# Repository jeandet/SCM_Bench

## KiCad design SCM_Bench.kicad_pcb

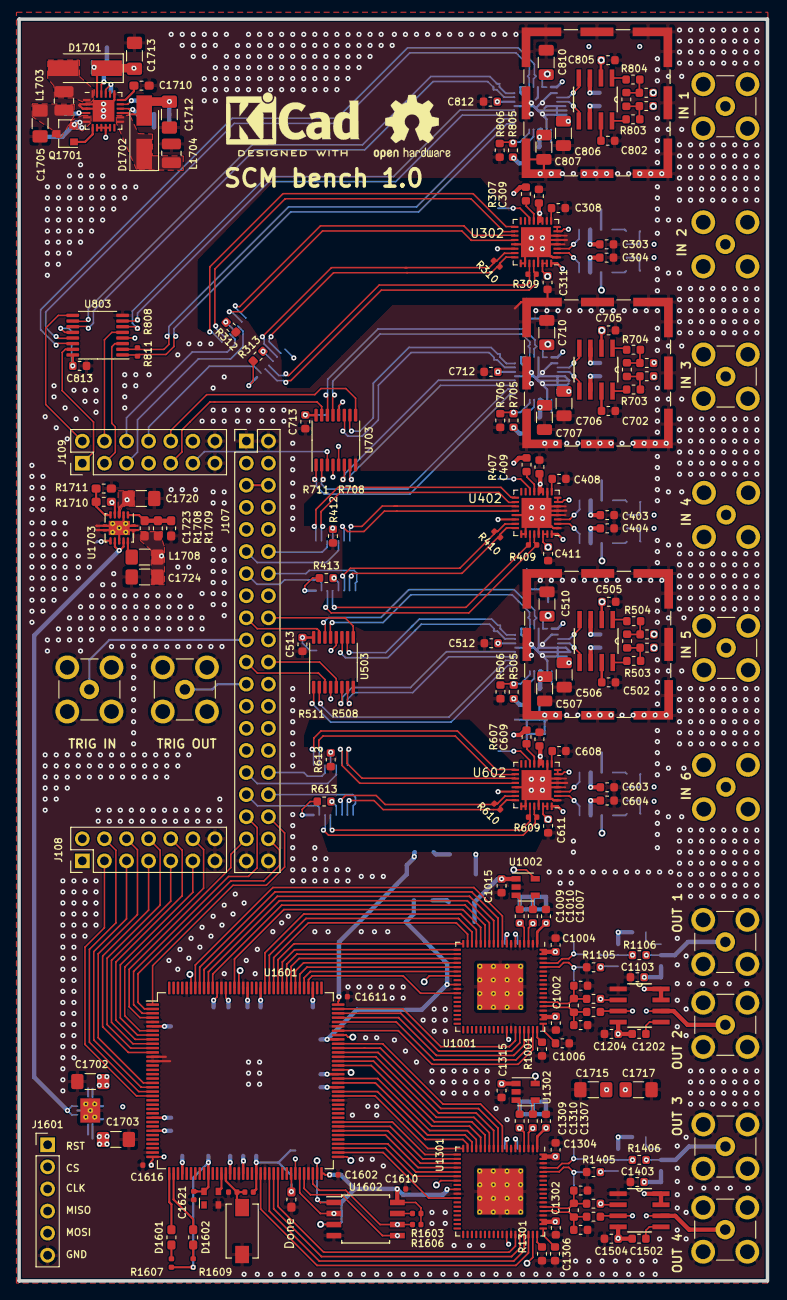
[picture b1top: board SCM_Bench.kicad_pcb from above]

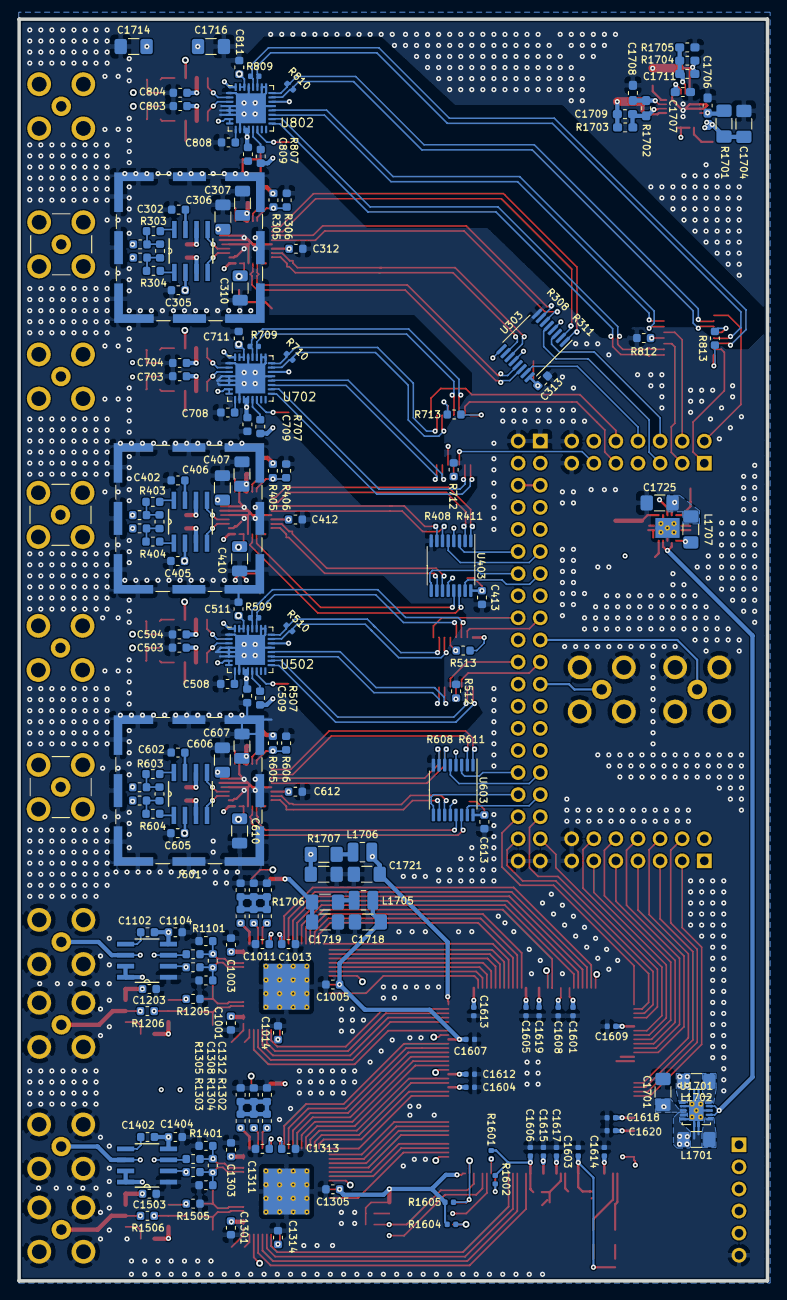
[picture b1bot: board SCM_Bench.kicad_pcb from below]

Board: 4 copper layers, 86.0 x 145.0 mm, 374 parts (186 on the bottom side), 313 nets.

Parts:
C301, C401, C501, C601, C701, C801: 66n; C_0603_1608Metric
C302, C305, C402, C405, C502, C505, C602, C605, C702, C705, C802, C805: 0.01u; C_0603_1608Metric
C303, C304, C308, C309, C311, C312, C313, C403, C404, C408, C409, C411, C412, C413, C503, C504, C508, C509, C511, C512, C513, C603, C604, C608, C609, C611, C612, C613, C703, C704, C708, C709, C711, C712, C713, C803, C804, C808, C809, C811, C812, C813, C1006, C1008, C1009, C1010, C1012, C1101, C1103, C1104, C1201, C1203, C1204, C1306, C1308, C1309, C1310, C1312, C1401, C1403, C1404, C1501, C1503, C1504: 0.1u; C_0603_1608Metric
C306, C307, C310, C406, C407, C410, C506, C507, C510, C606, C607, C610, C706, C707, C710, C806, C807, C810: 10u; C_1206_3216Metric
C1001, C1002, C1003, C1004, C1005, C1007, C1011, C1013, C1014, C1015, C1301, C1302, C1303, C1304, C1305, C1307, C1311, C1313, C1314, C1315: 100n; C_0603_1608Metric
C1102, C1202, C1402, C1502: 7p; C_0603_1608Metric
C1601, C1602, C1603, C1604, C1605, C1606, C1607, C1608, C1609, C1610, C1611, C1612, C1613, C1614, C1615, C1616, C1617, C1618, C1619, C1620, C1621, C1622: 100nF; C_0402_1005Metric
C1701, C1702, C1703, C1720, C1724, C1725: 10uF; C_1206_3216Metric_Pad1.42x1.75mm_HandSolder
C1704, C1705, C1714, C1715, C1716, C1717: 4.7uF; C_1206_3216Metric_Pad1.42x1.75mm_HandSolder
C1706: 100nF; C_0603_1608Metric_Pad1.05x0.95mm_HandSolder
C1707, C1708, C1709, C1710, C1711, C1723: C; C_0603_1608Metric_Pad1.05x0.95mm_HandSolder
C1712, C1713, C1718, C1719, C1721, C1722: 22uF; C_1206_3216Metric_Pad1.42x1.75mm_HandSolder
D1601, D1602: LED; R_0603_1608Metric_Pad1.05x0.95mm_HandSolder
D1701, D1702: D_Schottky; D_SMA_Handsoldering
DONE1601: LED; R_0603_1608Metric_Pad1.05x0.95mm_HandSolder
J101, J102, J103, J104, J105, J106, J110, J111, J901, J902, J903, J904: Conn_Coaxial; SMB_Jack_Vertical
J107: Conn_02x20_Odd_Even; PinHeader_2x20_P2.54mm_Vertical
J108, J109: Conn_02x07_Odd_Even; PinHeader_2x07_P2.54mm_Vertical
J301, J401, J501, J601, J701, J801: RF_Shield_One_Piece; Laird_Technologies_BMI-S-102_16.50x16.50mm
J1601: Conn_01x06; PinHeader_1x06_P2.54mm_Vertical
L1701, L1702, L1707, L1708: 2.2uH; L_1206_3216Metric_Pad1.42x1.75mm_HandSolder
L1703, L1704, L1705, L1706: 4.7uH; L_1008_2520Metric
LOGO101: Logo_Open_Hardware_Small; OSHW-Logo2_9.8x8mm_SilkScreen
LOGO102: Logo_Open_Hardware_Small; KiCad-Logo2_6mm_SilkScreen
Q1701: Q_PMOS_GSD; SOT-23
R301, R302, R303, R304, R401, R402, R403, R404, R501, R502, R503, R504, R601, R602, R603, R604, R701, R702, R703, R704, R801, R802, R803, R804: 1.7k; R_0603_1608Metric
R305, R306, R307, R312, R313, R405, R406, R407, R412, R413, R505, R506, R507, R512, R513, R605, R606, R607, R612, R613, R705, R706, R707, R712, R713, R805, R806, R807, R812, R813, R1001, R1301: 10k; R_0603_1608Metric
R308, R309, R310, R311, R408, R409, R410, R411, R508, R509, R510, R511, R608, R609, R610, R611, R708, R709, R710, R711, R808, R809, R810, R811: 100; R_0402_1005Metric
R1002, R1003, R1302, R1303: 50; R_0603_1608Metric
R1004, R1304: 1K; R_0603_1608Metric
R1005, R1305: 287; R_0603_1608Metric
R1101, R1102, R1201, R1202, R1401, R1402, R1501, R1502: 25; R_0603_1608Metric
R1103, R1104, R1203, R1204, R1403, R1404, R1503, R1504: 225; R_0603_1608Metric
R1105, R1106, R1205, R1206, R1405, R1406, R1505, R1506: 500; R_0603_1608Metric
R1601, R1603, R1604, R1605, R1606: 10k; R_0402_1005Metric
R1602, R1607, R1608, R1609: 2K2; R_0402_1005Metric
R1701: 100; R_1206_3216Metric_Pad1.42x1.75mm_HandSolder
R1702, R1703, R1704, R1705, R1708, R1709, R1710, R1711: R; R_0603_1608Metric_Pad1.05x0.95mm_HandSolder
R1706, R1707: 500m; R_1206_3216Metric_Pad1.42x1.75mm_HandSolder
SW1601: SW_Push; SW_SPST_EVQPE1
U301, U401, U501, U601, U701, U801: LT6600IS8; SOIC127P600X175-8N
U302, U402, U502, U602, U702, U802: LTC2386-18; QFN-32-1EP_5x5mm_P0.5mm_EP3.45x3.45mm
U303, U403, U503, U603, U703, U803: SN65LVDS1050PW; TSSOP-16_4.4x5mm_P0.65mm
U1001, U1301: AD9747BCPZ; LFCSP-72-1EP_10x10mm_P0.5mm_EP5.3x5.3mm_ThermalVias
U1002, U1302: SN65LVDS1DBV; SOT-23-5
U1101, U1201, U1401, U1501: AD8021; SOIC127P600X175-8N
U1601: ICE40HX1K-4K-TQ144; TQFP-144_20x20mm_P0.5mm
U1602: M25PX32-VMW; SOIJ-8_5.3x5.3mm_P1.27mm
U1603: ASDMB-xxxMHz; Oscillator_SMD_Abracon_ASDMB-4Pin_2.5x2.0mm
U1701, U1703: tps6240x; Texas_S-PVSON-N10_ThermalVias
U1702: TPS6513x; HVQFN-24-1EP_4x4mm_P0.5mm_EP2.5x2.5mm

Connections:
/2.5V: C310.1, C311.1, C410.1, C411.1, C510.1, C511.1, C610.1, C611.1, C710.1, C711.1, C810.1, C811.1, C1722.1, R1707.1, U302.30, U302.31, U402.30, U402.31, U502.30, U502.31, U602.30, U602.31, U702.30, U702.31, U802.30, U802.31
/3.3V: C1001.2, C1002.1, C1003.1, C1004.1, C1015.1, C1301.2, C1302.1, C1303.1, C1304.1, C1315.1, C1719.1, R1706.1, U1001.56, U1001.57, U1001.71, U1001.72, U1002.1, U1301.56, U1301.57, U1301.71, U1301.72, U1302.1
/5V: C304.2, C307.1, C309.1, C404.2, C407.1, C409.1, C504.2, C507.1, C509.1, C604.2, C607.1, C609.1, C704.2, C707.1, C709.1, C804.2, C807.1, C809.1, C1103.2, C1203.2, C1403.2, C1503.2, C1711.1, C1713.1, C1716.1, C1717.1, D1701.1, R1704.1, U301.3, U302.11, U302.12, U401.3, U402.11, U402.12, U501.3, U502.11, U502.12, U601.3, U602.11, U602.12, U701.3, U702.11, U702.12, U801.3, U802.11, U802.12, U1101.7, U1101.8, U1201.7, U1201.8, U1401.7, U1401.8, U1501.7, U1501.8, U1702.23
/#1.8V: C1007.1, C1011.1, C1013.1, C1014.1, C1307.1, C1311.1, C1313.1, C1314.1, C1725.1, L1707.2, R1004.2, R1304.2, R1710.1, U1001.1, U1001.6, U1001.8, U1001.47, U1301.1, U1301.6, U1301.8, U1301.47, U1703.4
/#2.5V: C312.1, C313.2, C412.1, C413.2, C512.1, C513.2, C612.1, C613.2, C712.1, C713.2, C812.1, C813.2, C1611.1, C1721.1, C1723.1, C1724.1, L1706.1, L1708.2, R305.2, R307.1, R313.1, R405.2, R407.1, R413.1, R505.2, R507.1, R513.1, R605.2, R607.1, R613.1, R705.2, R707.1, R713.1, R805.2, R807.1, R813.1, R1708.1, U302.22, U303.16, U402.22, U403.16, U502.22, U503.16, U602.22, U603.16, U702.22, U703.16, U802.22, U803.16, U1601.108
/-5V: C303.2, C403.2, C503.2, C603.2, C703.2, C803.2, C1102.1, C1104.1, C1202.1, C1204.1, C1402.1, C1404.1, C1502.1, C1504.1, C1709.2, C1712.1, C1714.1, C1715.1, D1702.2, R1703.2, U301.6, U401.6, U501.6, U601.6, U701.6, U801.6, U1101.4, U1201.4, U1401.4, U1501.4, U1702.15
/ADC1_CLK: J109.2, U803.9
/ADC1_CNV: J109.1, U803.15
/ADC1_DA: J109.3, U803.3
/ADC1_DCO: J109.4, U803.5
/ADC2_CLK: J109.7, U303.9
/ADC2_CNV: J109.8, U303.15
/ADC2_DA: J109.6, U303.3
/ADC2_DCO: J109.5, U303.5
/ADC3_CLK: J109.10, U703.9
/ADC3_CNV: J109.9, U703.15
/ADC3_DA: J109.11, U703.3
/ADC3_DCO: J109.12, U703.5
/ADC4_CLK: J107.14, U403.9
/ADC4_CNV: J107.13, U403.15
/ADC4_DA: J107.12, U403.3
/ADC4_DCO: J107.11, U403.5
/ADC5_CLK: J107.18, U503.9
/ADC5_CNV: J107.17, U503.15
/ADC5_DA: J107.21, U503.3
/ADC5_DCO: J107.22, U503.5
/ADC6_CLK: J107.34, U603.9
/ADC6_CNV: J107.33, U603.15
/ADC6_DA: J107.32, U603.3
/ADC6_DCO: J107.31, U603.5
/DAC_FPGA_IO0: J107.36, U1601.1
/DAC_FPGA_IO1: J107.38, U1601.2
/DAC_FPGA_IO2: J107.35, U1601.3
/DAC_FPGA_IO3: J107.37, U1601.4
/DAC_FPGA_IO4: J108.12, U1601.7
/DAC_FPGA_IO5: J108.11, U1601.8
/DAC_FPGA_IO6: J108.10, U1601.9
/DAC_FPGA_IO7: J108.9, U1601.10
/DAC_FPGA_IO8: J108.8, U1601.11
/DAC_FPGA_IO9: J108.7, U1601.12
/DAC_FPGA_IO10: J108.6, U1601.19
/DAC_FPGA_IO11: J108.5, U1601.20
/DAC_FPGA_IO12: J108.4, U1601.21
/DAC_FPGA_IO13: J108.3, U1601.22
/FLASH_CLK: J107.28, J1601.3, R1606.2, U1601.70, U1602.6
/FLASH_MISO: J107.29, J1601.4, U1601.67, U1602.2
/FLASH_MOSI: J107.30, J1601.5, U1601.68, U1602.5
/FLASH_SS: J107.27, J1601.2, R1605.2, U1601.71, U1602.1
/FLASH_~CRESET: J107.26, J1601.1, R1601.2, U1601.66
/IOB_11: J107.23, J111.1
/IOB_15: J107.19, J110.1
/Sheet5F3E1819/CH1_IN+: J101.1, R801.2
/Sheet5F3E1819/CH1_IN-: J101.2, R802.2
/Sheet5F3E1819/CH2_IN+: J102.1, R301.2
/Sheet5F3E1819/CH2_IN-: J102.2, R302.2
/Sheet5F3E1819/CH3_IN+: J103.1, R701.2
/Sheet5F3E1819/CH3_IN-: J103.2, R702.2
/Sheet5F3E1819/CH4_IN+: J104.1, R401.2
/Sheet5F3E1819/CH4_IN-: J104.2, R402.2
/Sheet5F3E1819/CH5_IN+: J105.1, R501.2
/Sheet5F3E1819/CH5_IN-: J105.2, R502.2
/Sheet5F3E1819/CH6_IN+: J106.1, R601.2
/Sheet5F3E1819/CH6_IN-: J106.2, R602.2
/Sheet5F3E1819/Sheet5F3E1AE4/ADC1_OUT_IN+: U301.4, U302.2
/Sheet5F3E1819/Sheet5F3E1AE4/ADC1_OUT_IN-: U301.5, U302.3
/Sheet5F3E1819/Sheet5F3E1AE4/CLK+: R310.2, U302.24, U303.10
/Sheet5F3E1819/Sheet5F3E1AE4/CLK-: R310.1, U302.23, U303.11
/Sheet5F3E1819/Sheet5F3E1AE4/CNV+: R309.2, U302.28, U303.14
/Sheet5F3E1819/Sheet5F3E1AE4/CNV-: R309.1, U302.27, U303.13
/Sheet5F3E1819/Sheet5F3E1AE4/DA+: R311.2, U302.18, U303.2
/Sheet5F3E1819/Sheet5F3E1AE4/DA-: R311.1, U302.17, U303.1
/Sheet5F3E1819/Sheet5F3E1AE4/DCO+: R308.2, U302.20, U303.6
/Sheet5F3E1819/Sheet5F3E1AE4/DCO-: R308.1, U302.19, U303.7
/Sheet5F3E1819/sheet5F766F53/ADC1_OUT_IN+: U601.4, U602.2
/Sheet5F3E1819/sheet5F766F53/ADC1_OUT_IN-: U601.5, U602.3
/Sheet5F3E1819/sheet5F766F53/CLK+: R610.2, U602.24, U603.10
/Sheet5F3E1819/sheet5F766F53/CLK-: R610.1, U602.23, U603.11
/Sheet5F3E1819/sheet5F766F53/CNV+: R609.2, U602.28, U603.14
/Sheet5F3E1819/sheet5F766F53/CNV-: R609.1, U602.27, U603.13
/Sheet5F3E1819/sheet5F766F53/DA+: R611.2, U602.18, U603.2
/Sheet5F3E1819/sheet5F766F53/DA-: R611.1, U602.17, U603.1
/Sheet5F3E1819/sheet5F766F53/DCO+: R608.2, U602.20, U603.6
/Sheet5F3E1819/sheet5F766F53/DCO-: R608.1, U602.19, U603.7
/Sheet5F3E1819/sheet5F7670FC/ADC1_OUT_IN+: U401.4, U402.2
/Sheet5F3E1819/sheet5F7670FC/ADC1_OUT_IN-: U401.5, U402.3
/Sheet5F3E1819/sheet5F7670FC/CLK+: R410.2, U402.24, U403.10
/Sheet5F3E1819/sheet5F7670FC/CLK-: R410.1, U402.23, U403.11
/Sheet5F3E1819/sheet5F7670FC/CNV+: R409.2, U402.28, U403.14
/Sheet5F3E1819/sheet5F7670FC/CNV-: R409.1, U402.27, U403.13
/Sheet5F3E1819/sheet5F7670FC/DA+: R411.2, U402.18, U403.2
/Sheet5F3E1819/sheet5F7670FC/DA-: R411.1, U402.17, U403.1
/Sheet5F3E1819/sheet5F7670FC/DCO+: R408.2, U402.20, U403.6
/Sheet5F3E1819/sheet5F7670FC/DCO-: R408.1, U402.19, U403.7
/Sheet5F3E1819/sheet5F7672A2/ADC1_OUT_IN+: U801.4, U802.2
/Sheet5F3E1819/sheet5F7672A2/ADC1_OUT_IN-: U801.5, U802.3
/Sheet5F3E1819/sheet5F7672A2/CLK+: R810.2, U802.24, U803.10
/Sheet5F3E1819/sheet5F7672A2/CLK-: R810.1, U802.23, U803.11
/Sheet5F3E1819/sheet5F7672A2/CNV+: R809.2, U802.28, U803.14
/Sheet5F3E1819/sheet5F7672A2/CNV-: R809.1, U802.27, U803.13
/Sheet5F3E1819/sheet5F7672A2/DA+: R811.2, U802.18, U803.2
/Sheet5F3E1819/sheet5F7672A2/DA-: R811.1, U802.17, U803.1
/Sheet5F3E1819/sheet5F7672A2/DCO+: R808.2, U802.20, U803.6
/Sheet5F3E1819/sheet5F7672A2/DCO-: R808.1, U802.19, U803.7
/Sheet5F3E1819/sheet5F76778E/ADC1_OUT_IN+: U701.4, U702.2
/Sheet5F3E1819/sheet5F76778E/ADC1_OUT_IN-: U701.5, U702.3
/Sheet5F3E1819/sheet5F76778E/CLK+: R710.2, U702.24, U703.10
/Sheet5F3E1819/sheet5F76778E/CLK-: R710.1, U702.23, U703.11
/Sheet5F3E1819/sheet5F76778E/CNV+: R709.2, U702.28, U703.14
/Sheet5F3E1819/sheet5F76778E/CNV-: R709.1, U702.27, U703.13
/Sheet5F3E1819/sheet5F76778E/DA+: R711.2, U702.18, U703.2
/Sheet5F3E1819/sheet5F76778E/DA-: R711.1, U702.17, U703.1
/Sheet5F3E1819/sheet5F76778E/DCO+: R708.2, U702.20, U703.6
/Sheet5F3E1819/sheet5F76778E/DCO-: R708.1, U702.19, U703.7
/Sheet5F3E1819/sheet5F767499/ADC1_OUT_IN+: U501.4, U502.2
/Sheet5F3E1819/sheet5F767499/ADC1_OUT_IN-: U501.5, U502.3
/Sheet5F3E1819/sheet5F767499/CLK+: R510.2, U502.24, U503.10
/Sheet5F3E1819/sheet5F767499/CLK-: R510.1, U502.23, U503.11
/Sheet5F3E1819/sheet5F767499/CNV+: R509.2, U502.28, U503.14
/Sheet5F3E1819/sheet5F767499/CNV-: R509.1, U502.27, U503.13
/Sheet5F3E1819/sheet5F767499/DA+: R511.2, U502.18, U503.2
/Sheet5F3E1819/sheet5F767499/DA-: R511.1, U502.17, U503.1
/Sheet5F3E1819/sheet5F767499/DCO+: R508.2, U502.20, U503.6
/Sheet5F3E1819/sheet5F767499/DCO-: R508.1, U502.19, U503.7
/Sheet5F420A25/DAC1_D0: U1001.24, U1601.113
/Sheet5F420A25/DAC1_D1: U1001.23, U1601.114
/Sheet5F420A25/DAC1_D2: U1001.22, U1601.115
/Sheet5F420A25/DAC1_D3: U1001.21, U1601.116
/Sheet5F420A25/DAC1_D4: U1001.20, U1601.117
/Sheet5F420A25/DAC1_D5: U1001.19, U1601.118
/Sheet5F420A25/DAC1_D6: U1001.18, U1601.119
/Sheet5F420A25/DAC1_D7: U1001.17, U1601.120
/Sheet5F420A25/DAC1_D8: U1001.16, U1601.121
/Sheet5F420A25/DAC1_D9: U1001.15, U1601.122
/Sheet5F420A25/DAC1_D10: U1001.14, U1601.129
/Sheet5F420A25/DAC1_D11: U1001.13, U1601.134
/Sheet5F420A25/DAC1_D12: U1001.12, U1601.135
/Sheet5F420A25/DAC1_D13: U1001.11, U1601.136
/Sheet5F420A25/DAC1_D14: U1001.10, U1601.137
/Sheet5F420A25/DAC1_D15: U1001.9, U1601.138
/Sheet5F420A25/DAC2_D0: U1301.24, U1601.75
/Sheet5F420A25/DAC2_D1: U1301.23, U1601.76
/Sheet5F420A25/DAC2_D2: U1301.22, U1601.78
/Sheet5F420A25/DAC2_D3: U1301.21, U1601.79
/Sheet5F420A25/DAC2_D4: U1301.20, U1601.80
/Sheet5F420A25/DAC2_D5: U1301.19, U1601.81
/Sheet5F420A25/DAC2_D6: U1301.18, U1601.87
/Sheet5F420A25/DAC2_D7: U1301.17, U1601.88
/Sheet5F420A25/DAC2_D8: U1301.16, U1601.90
/Sheet5F420A25/DAC2_D9: U1301.15, U1601.91
/Sheet5F420A25/DAC2_D10: U1301.14, U1601.94
/Sheet5F420A25/DAC2_D11: U1301.13, U1601.95
/Sheet5F420A25/DAC2_D12: U1301.12, U1601.96
/Sheet5F420A25/DAC2_D13: U1301.11, U1601.97
/Sheet5F420A25/DAC2_D14: U1301.10, U1601.98
/Sheet5F420A25/DAC2_D15: U1301.9, U1601.99
/Sheet5F420A25/Sheet5F420DB3/CSB: U1001.52, U1601.104
/Sheet5F420A25/Sheet5F420DB3/DAC_CLK_N: C1009.2, U1002.3
/Sheet5F420A25/Sheet5F420DB3/DAC_CLK_P: C1010.2, U1002.4
/Sheet5F420A25/Sheet5F420DB3/OUT1: J902.1, R1106.1, U1101.6
/Sheet5F420A25/Sheet5F420DB3/OUT2: J901.1, R1206.1, U1201.6
/Sheet5F420A25/Sheet5F420DB3/Sheet5F4D5B79/IN+: C1101.2, R1101.2, R1103.2, U1001.69
/Sheet5F420A25/Sheet5F420DB3/Sheet5F4D5B79/IN-: C1101.1, R1102.2, R1104.2, U1001.68
/Sheet5F420A25/Sheet5F420DB3/sheet5F53F8D8/IN+: C1201.2, R1201.2, R1203.2, U1001.59
/Sheet5F420A25/Sheet5F420DB3/sheet5F53F8D8/IN-: C1201.1, R1202.2, R1204.2, U1001.60
/Sheet5F420A25/sheet5F62EEDA/BP: C1622.1, R1608.2, SW1601.2, U1601.50
/Sheet5F420A25/sheet5F62EEDA/DAC1_CLK: U1002.5, U1601.139
/Sheet5F420A25/sheet5F62EEDA/DAC1_DCO: U1001.25, U1601.128
/Sheet5F420A25/sheet5F62EEDA/DAC1_IQSEL: U1001.29, U1601.112
/Sheet5F420A25/sheet5F62EEDA/DAC1_RST: U1001.53, U1601.102
/Sheet5F420A25/sheet5F62EEDA/DAC1_SCLK: U1001.51, U1601.105
/Sheet5F420A25/sheet5F62EEDA/DAC1_SDIO: U1001.50, U1601.106
/Sheet5F420A25/sheet5F62EEDA/DAC1_SDO: U1001.49, U1601.107
/Sheet5F420A25/sheet5F62EEDA/DAC2_CLK: U1302.5, U1601.101
/Sheet5F420A25/sheet5F62EEDA/DAC2_DCO: U1301.25, U1601.93
/Sheet5F420A25/sheet5F62EEDA/DAC2_IQSEL: U1301.29, U1601.74
/Sheet5F420A25/sheet5F62EEDA/DAC2_RST: U1301.53, U1601.73
/Sheet5F420A25/sheet5F62EEDA/DAC2_SCLK: U1301.51, U1601.60
/Sheet5F420A25/sheet5F62EEDA/DAC2_SDIO: U1301.50, U1601.61
/Sheet5F420A25/sheet5F62EEDA/DAC2_SDO: U1301.49, U1601.62
/Sheet5F420A25/sheet5F62EEDA/FLASH_CDONE: DONE1601.2, R1602.2, U1601.65
/Sheet5F420A25/sheet5F62EEDA/FPGA_CLK: U1601.49, U1603.3
/Sheet5F420A25/sheet5F62EEDA/LED1: D1601.1, U1601.37
/Sheet5F420A25/sheet5F62EEDA/LED2: D1602.1, U1601.38
/Sheet5F420A25/sheet5F604603/CSB: U1301.52, U1601.58
/Sheet5F420A25/sheet5F604603/DAC_CLK_N: C1309.2, U1302.3
/Sheet5F420A25/sheet5F604603/DAC_CLK_P: C1310.2, U1302.4
/Sheet5F420A25/sheet5F604603/OUT1: J904.1, R1406.1, U1401.6
/Sheet5F420A25/sheet5F604603/OUT2: J903.1, R1506.1, U1501.6
/Sheet5F420A25/sheet5F604603/Sheet5F4D5B79/IN+: C1401.2, R1401.2, R1403.2, U1301.69
/Sheet5F420A25/sheet5F604603/Sheet5F4D5B79/IN-: C1401.1, R1402.2, R1404.2, U1301.68
/Sheet5F420A25/sheet5F604603/sheet5F53F8D8/IN+: C1501.2, R1501.2, R1503.2, U1301.59
/Sheet5F420A25/sheet5F604603/sheet5F53F8D8/IN-: C1501.1, R1502.2, R1504.2, U1301.60
/USB_3.3V: J107.5, J107.6
/USB_5V: C1701.1, C1704.1, C1720.1, J107.3, J107.4, Q1701.2, R1701.2, U1701.3, U1701.7, U1701.9, U1702.5, U1702.6, U1702.8, U1702.9, U1702.10, U1702.11, U1703.3, U1703.7, U1703.9
GND: C302.2, C303.1, C304.1, C305.2, C306.2, C307.2, C308.2, C309.2, C310.2, C311.2, C312.2, C313.1, C402.2, C403.1, C404.1, C405.2, C406.2, C407.2, C408.2, C409.2, C410.2, C411.2, C412.2, C413.1, C502.2, C503.1, C504.1, C505.2, C506.2, C507.2, C508.2, C509.2, C510.2, C511.2, C512.2, C513.1, C602.2, C603.1, C604.1, C605.2, C606.2, C607.2, C608.2, C609.2, C610.2, C611.2, C612.2, C613.1, C702.2, C703.1, C704.1, C705.2, C706.2, C707.2, C708.2, C709.2, C710.2, C711.2, C712.2, C713.1, C802.2, C803.1, C804.1, C805.2, C806.2, C807.2, C808.2, C809.2, C810.2, C811.2, C812.2, C813.1, C1001.1, C1002.2, C1003.2, C1004.2, C1005.2, C1006.1, C1007.2, C1008.2, C1011.2, C1012.2, C1013.2, C1014.2, C1015.2, C1103.1, C1104.2, C1203.1, C1204.2, C1301.1, C1302.2, C1303.2, C1304.2, C1305.2, C1306.1, C1307.2, C1308.2, C1311.2, C1312.2, C1313.2, C1314.2, C1315.2, C1403.1, C1404.2, C1503.1, C1504.2, C1601.2, C1602.2, C1603.2, C1604.2, C1605.2, C1606.2, C1607.2, C1608.2, C1609.2, C1610.2, C1611.2, C1612.2, C1613.2, C1614.2, C1615.2, C1616.2, C1617.2, C1618.2, C1619.2, C1620.2, C1621.2, C1622.2, C1701.2, C1702.2, C1703.2, C1704.2, C1705.2, C1706.2, C1707.2, C1708.2, C1710.2, C1712.2, C1713.2, C1714.2, C1715.2, C1716.2, C1717.2, C1718.2, C1719.2, C1720.2, C1721.2, C1722.2, C1724.2, C1725.2, DONE1601.1, J107.1, J107.2, J107.39, J107.40, J108.13, J108.14, J109.13, J109.14, J110.2, J111.2, J301.1, J401.1, J501.1, J601.1, J701.1, J801.1, J901.2, J902.2, J903.2, J904.2, J1601.6, L1704.2, R306.1, R312.1, R406.1, R412.1, R506.1, R512.1, R606.1, R612.1, R706.1, R712.1, R806.1, R812.1, R1001.2, R1005.1, R1101.1, R1102.1, R1105.1, R1201.1, R1202.1, R1205.1, R1301.2, R1305.1, R1401.1, R1402.1, R1405.1, R1501.1, R1502.1, R1505.1, R1705.2, R1709.2, R1711.2, SW1601.1, U302.1, U302.4, U302.5, U302.6, U302.10, U302.21, U302.25, U302.26, U302.29, U302.33, U303.8, U402.1, U402.4, U402.5, U402.6, U402.10, U402.21, U402.25, U402.26, U402.29, U402.33, U403.8, U502.1, U502.4, U502.5, U502.6, U502.10, U502.21, U502.25, U502.26, U502.29, U502.33, U503.8, U602.1, U602.4, U602.5, U602.6, U602.10, U602.21, U602.25, U602.26, U602.29, U602.33, U603.8, U702.1, U702.4, U702.5, U702.6, U702.10, U702.21, U702.25, U702.26, U702.29, U702.33, U703.8, U802.1, U802.4, U802.5, U802.6, U802.10, U802.21, U802.25, U802.26, U802.29, U802.33, U803.8, U1001.2, U1001.5, U1001.7, U1001.28, U1001.48, U1001.58, U1001.61, U1001.64, U1001.67, U1001.70, U1001.73, U1002.2, U1101.1, U1201.1, U1301.2, U1301.5, U1301.7, U1301.28, U1301.48, U1301.58, U1301.61, U1301.64, U1301.67, U1301.70, U1301.73, U1302.2, U1401.1, U1501.1, U1601.5, U1601.13, U1601.14, U1601.35, U1601.53, U1601.59, U1601.69, U1601.86, U1601.103, U1601.127, U1601.132, U1601.140, U1602.4, U1603.2, U1701.2, U1701.5, U1701.8, U1701.11, U1702.2, U1702.3, U1702.19, U1702.25, U1703.2, U1703.8, U1703.11
unnamed: C301.1, R301.1, R303.2
unnamed: C301.2, R302.1, R304.2
unnamed: C302.1, U301.7
unnamed: C305.1, U301.2, U302.32
unnamed: C306.1, U302.7, U302.8
unnamed: C308.1, U302.9
unnamed: C401.1, R401.1, R403.2
unnamed: C401.2, R402.1, R404.2
unnamed: C402.1, U401.7
unnamed: C405.1, U401.2, U402.32
unnamed: C406.1, U402.7, U402.8
unnamed: C408.1, U402.9
unnamed: C501.1, R501.1, R503.2
unnamed: C501.2, R502.1, R504.2
unnamed: C502.1, U501.7
unnamed: C505.1, U501.2, U502.32
unnamed: C506.1, U502.7, U502.8
unnamed: C508.1, U502.9
unnamed: C601.1, R601.1, R603.2
unnamed: C601.2, R602.1, R604.2
unnamed: C602.1, U601.7
unnamed: C605.1, U601.2, U602.32
unnamed: C606.1, U602.7, U602.8
unnamed: C608.1, U602.9
unnamed: C701.1, R701.1, R703.2
unnamed: C701.2, R702.1, R704.2
unnamed: C702.1, U701.7
unnamed: C705.1, U701.2, U702.32
unnamed: C706.1, U702.7, U702.8
unnamed: C708.1, U702.9
unnamed: C801.1, R801.1, R803.2
unnamed: C801.2, R802.1, R804.2
unnamed: C802.1, U801.7
unnamed: C805.1, U801.2, U802.32
unnamed: C806.1, U802.7, U802.8
unnamed: C808.1, U802.9
unnamed: C1006.2, U1001.55
unnamed: C1008.1, C1012.1, R1002.1, R1003.2, R1004.1, R1005.2
unnamed: C1009.1, R1002.2, U1001.4
unnamed: C1010.1, R1003.1, U1001.3
unnamed: C1102.2, U1101.5
unnamed: C1202.2, U1201.5
unnamed: C1306.2, U1301.55
unnamed: C1308.1, C1312.1, R1302.1, R1303.2, R1304.1, R1305.2
unnamed: C1309.1, R1302.2, U1301.4
unnamed: C1310.1, R1303.1, U1301.3
unnamed: C1402.2, U1401.5
unnamed: C1502.2, U1501.5
unnamed: C1705.1, L1703.1, Q1701.3
unnamed: C1706.1, R1701.1, U1702.4
unnamed: C1707.1, U1702.21
unnamed: C1708.1, R1702.1, U1702.17
unnamed: C1709.1, R1702.2, R1703.1, U1702.16
unnamed: C1710.1, U1702.18
unnamed: C1711.2, R1704.2, R1705.1, U1702.22
unnamed: C1723.2, R1708.2, R1709.1, U1703.1
unnamed: D1601.2, R1607.2
unnamed: D1602.2, R1609.2
unnamed: D1701.2, L1703.2, U1702.1, U1702.24
unnamed: D1702.1, L1704.1, U1702.13, U1702.14
unnamed: L1701.1, U1701.6
unnamed: L1702.1, U1701.10
unnamed: L1705.2, R1706.2
unnamed: L1706.2, R1707.2
unnamed: L1707.1, U1703.6
unnamed: L1708.1, U1703.10
unnamed: Q1701.1, U1702.7
unnamed: R303.1, U301.8
unnamed: R304.1, U301.1
unnamed: R305.1, R306.2, U302.14
unnamed: R307.2, U302.13
unnamed: R312.2, U303.4
unnamed: R313.2, U303.12
unnamed: R403.1, U401.8
unnamed: R404.1, U401.1
unnamed: R405.1, R406.2, U402.14
unnamed: R407.2, U402.13
unnamed: R412.2, U403.4
unnamed: R413.2, U403.12
unnamed: R503.1, U501.8
unnamed: R504.1, U501.1
unnamed: R505.1, R506.2, U502.14
unnamed: R507.2, U502.13
unnamed: R512.2, U503.4
unnamed: R513.2, U503.12
unnamed: R603.1, U601.8
unnamed: R604.1, U601.1
unnamed: R605.1, R606.2, U602.14
unnamed: R607.2, U602.13
unnamed: R612.2, U603.4
unnamed: R613.2, U603.12
unnamed: R703.1, U701.8
unnamed: R704.1, U701.1
unnamed: R705.1, R706.2, U702.14
unnamed: R707.2, U702.13
unnamed: R712.2, U703.4
unnamed: R713.2, U703.12
unnamed: R803.1, U801.8
unnamed: R804.1, U801.1
unnamed: R805.1, R806.2, U802.14
unnamed: R807.2, U802.13
unnamed: R812.2, U803.4
unnamed: R813.2, U803.12
unnamed: R1001.1, U1001.54
unnamed: R1103.1, R1106.2, U1101.3
unnamed: R1104.1, R1105.2, U1101.2
unnamed: R1203.1, R1206.2, U1201.3
unnamed: R1204.1, R1205.2, U1201.2
unnamed: R1301.1, U1301.54
unnamed: R1403.1, R1406.2, U1401.3
unnamed: R1404.1, R1405.2, U1401.2
unnamed: R1503.1, R1506.2, U1501.3
unnamed: R1504.1, R1505.2, U1501.2
unnamed: R1603.2, U1602.7
unnamed: R1604.2, U1602.3
unnamed: R1710.2, R1711.1, U1703.5
VCC: C1612.1, C1613.1, C1614.1, C1615.1, C1616.1, C1617.1, C1618.1, C1619.1, C1703.1, L1701.2, U1601.27, U1601.36, U1601.40, U1601.51, U1601.54, U1601.92, U1601.111, U1601.126, U1701.4
VCCIO_0: C1005.1, C1305.1, C1601.1, C1602.1, C1603.1, C1604.1, C1605.1, C1606.1, C1607.1, C1608.1, C1609.1, C1610.1, C1620.1, C1621.1, C1702.1, C1718.1, L1702.2, L1705.1, R1601.1, R1602.1, R1603.1, R1604.1, R1605.1, R1606.1, R1607.1, R1608.1, R1609.1, U1001.27, U1301.27, U1601.6, U1601.30, U1601.46, U1601.57, U1601.72, U1601.89, U1601.100, U1601.123, U1601.131, U1601.133, U1602.8, U1603.4, U1701.1

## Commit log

2020-08-20 Schematic for ADC and DAC ready, layout for each ADC and DAC channel done
2020-08-20 initial placement of all ADC/DAC blocks and added FPGA
2020-08-21 Layout done for ADC + LVDS and DAC -> FPGA
2020-08-23 Added #3.3V and #1.2V supply, completed ADC to USB board layout, added DAC FPGA to USB board bus.
2020-08-24 Layout complete, needs silk screen cleanup and few checks
2020-08-25 PCB ready for review
2020-08-25 Fixed mistake on one ADC chan power line
2020-08-26 Last cleanups
2020-08-27 Desing as ordered for V1.0
